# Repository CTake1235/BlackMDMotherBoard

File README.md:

# 黒MDマザーボード設計構想
> by しーたけ @C_Take_e
> since 2024/03/05
## 黒MDとは？
```
茨城高専ロボット部にて2017年に開発・製造されたMD。レジストが黒いのでそう呼ばれている。
定格12V駆動。I2C信号またはRS-485で動作する（基本I2Cでしか使わん）。
ロボコンで用いる各種モータを振り回せるため、何も考えずに使いまわされ続けている。
```
## コンセプト
- **やさしいマザボ**
## 詳細な構想
- ケーブルを介した連結が可能な、4枚挿しコンパクトマザボ
	- 単純なケーブルでできる、「マザー連結用」のようなケーブルを不要とする
	
- 黒MD初期マザーに準拠したコネクタ配線
- XAコネクタとXT60コネクタ（現在部活で主流のもの）を用いる
- 電源系の配線はタテ、信号系はヨコ
	- 電源系をヨコにすると、水平方向に広げる回路ボックスと相性が悪い
		- 縦に広がる回路ボックス: 基板を縦に積みつつコネクタを横に出して省面積化できる
		- 横に広がる回路ボックス(現在): 基板を水平方向に並べるので、コネクタがヨコ向きだとほかの基板と干渉するなど問題が起きやすい
	- 信号系はタテにすると基板の配置上MDとツメロック部分が干渉するなど、かえって邪魔になる
		- また、信号線は電源線に比べて細く曲げやすいため、ケーブルが他の基板などと干渉しにくい
- 100mm \* 100mmに収める
	- これは発注金額の問題
	- 実際には1.27(0.5mil)の倍数: 99.06mmを1辺とする設計にすることで配線の対称性などを保つ
- https://www.figma.com/file/h6nRyaCE1Uanp6SJ3a7Op9/2024%E9%BB%92MD%E3%83%9E%E3%82%B6%E3%83%BC?type=whiteboard&node-id=0%3A1&t=XtIcsm7LwBn8oLYL-1
	- figmaに謎図あります

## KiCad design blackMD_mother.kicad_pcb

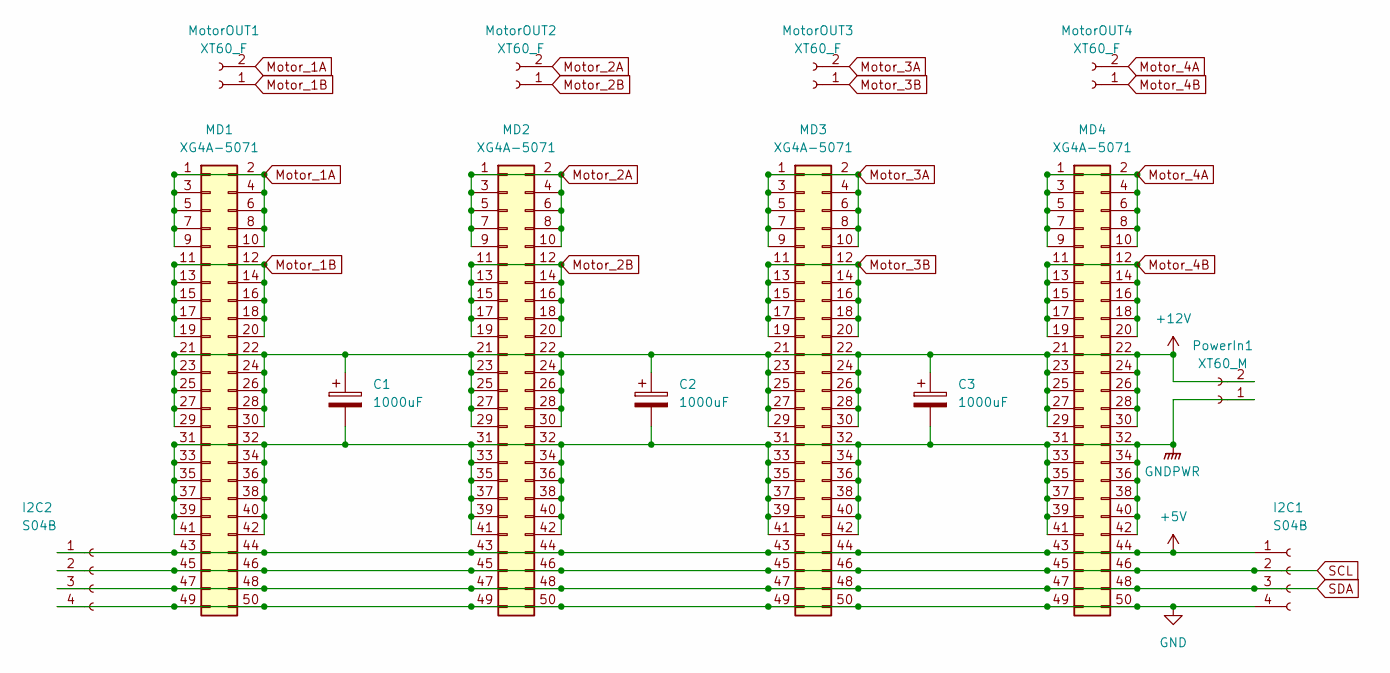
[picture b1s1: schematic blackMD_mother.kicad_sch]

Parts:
C1, C2, C3: 1000uF; CP_Radial_D10.0mm_P5.00mm
I2C1, I2C2: S04B; JST_XA_S04B-XASK-1_1x04_P2.50mm_Horizontal
MD1, MD2, MD3, MD4: XG4A-5071; PinSocket_2x25_P2.54mm_Vertical
MotorOUT1, MotorOUT2, MotorOUT3, MotorOUT4: XT60_F; AMASS_XT60-F_1x02_P7.20mm_Vertical
PowerIn1: XT60_M; AMASS_XT60-M_1x02_P7.20mm_Vertical

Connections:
+5V: I2C1.1, I2C2.1, MD1.43, MD1.44, MD2.43, MD2.44, MD3.43, MD3.44, MD4.43, MD4.44
+12V: C1.1, C2.1, C3.1, MD1.21, MD1.22, MD1.23, MD1.24, MD1.25, MD1.26, MD1.27, MD1.28, MD1.29, MD1.30, MD2.21, MD2.22, MD2.23, MD2.24, MD2.25, MD2.26, MD2.27, MD2.28, MD2.29, MD2.30, MD3.21, MD3.22, MD3.23, MD3.24, MD3.25, MD3.26, MD3.27, MD3.28, MD3.29, MD3.30, MD4.21, MD4.22, MD4.23, MD4.24, MD4.25, MD4.26, MD4.27, MD4.28, MD4.29, MD4.30, PowerIn1.2
GND: I2C1.4, I2C2.4, MD1.49, MD1.50, MD2.49, MD2.50, MD3.49, MD3.50, MD4.49, MD4.50
GNDPWR: C1.2, C2.2, C3.2, MD1.31, MD1.32, MD1.33, MD1.34, MD1.35, MD1.36, MD1.37, MD1.38, MD1.39, MD1.40, MD1.41, MD1.42, MD2.31, MD2.32, MD2.33, MD2.34, MD2.35, MD2.36, MD2.37, MD2.38, MD2.39, MD2.40, MD2.41, MD2.42, MD3.31, MD3.32, MD3.33, MD3.34, MD3.35, MD3.36, MD3.37, MD3.38, MD3.39, MD3.40, MD3.41, MD3.42, MD4.31, MD4.32, MD4.33, MD4.34, MD4.35, MD4.36, MD4.37, MD4.38, MD4.39, MD4.40, MD4.41, MD4.42, PowerIn1.1
Motor_1A: MD1.1, MD1.2, MD1.3, MD1.4, MD1.5, MD1.6, MD1.7, MD1.8, MD1.9, MD1.10, MotorOUT1.2
Motor_1B: MD1.11, MD1.12, MD1.13, MD1.14, MD1.15, MD1.16, MD1.17, MD1.18, MD1.19, MD1.20, MotorOUT1.1
Motor_2A: MD2.1, MD2.2, MD2.3, MD2.4, MD2.5, MD2.6, MD2.7, MD2.8, MD2.9, MD2.10, MotorOUT2.2
Motor_2B: MD2.11, MD2.12, MD2.13, MD2.14, MD2.15, MD2.16, MD2.17, MD2.18, MD2.19, MD2.20, MotorOUT2.1
Motor_3A: MD3.1, MD3.2, MD3.3, MD3.4, MD3.5, MD3.6, MD3.7, MD3.8, MD3.9, MD3.10, MotorOUT3.2
Motor_3B: MD3.11, MD3.12, MD3.13, MD3.14, MD3.15, MD3.16, MD3.17, MD3.18, MD3.19, MD3.20, MotorOUT3.1
Motor_4A: MD4.1, MD4.2, MD4.3, MD4.4, MD4.5, MD4.6, MD4.7, MD4.8, MD4.9, MD4.10, MotorOUT4.2
Motor_4B: MD4.11, MD4.12, MD4.13, MD4.14, MD4.15, MD4.16, MD4.17, MD4.18, MD4.19, MD4.20, MotorOUT4.1
SCL: I2C1.2, I2C2.2, MD1.45, MD1.46, MD2.45, MD2.46, MD3.45, MD3.46, MD4.45, MD4.46
SDA: I2C1.3, I2C2.3, MD1.47, MD1.48, MD2.47, MD2.48, MD3.47, MD3.48, MD4.47, MD4.48

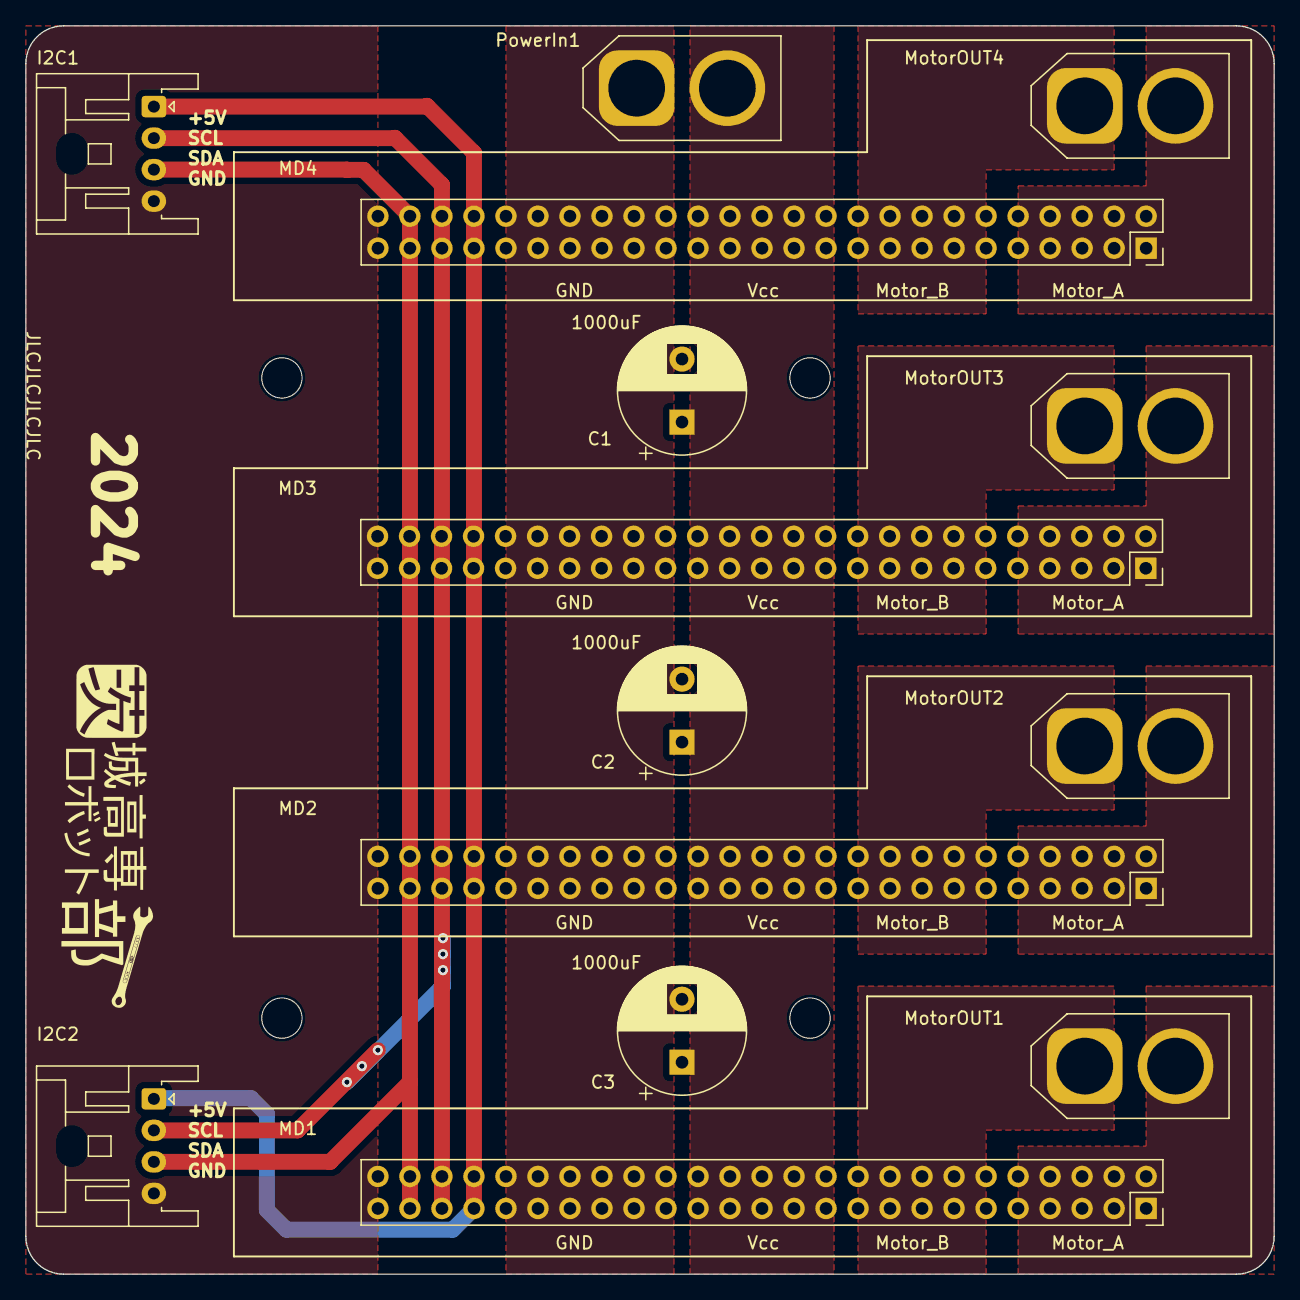
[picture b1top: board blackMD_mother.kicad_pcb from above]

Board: 2 copper layers, 99.1 x 99.1 mm, 14 parts (0 on the bottom side), 14 nets.

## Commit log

2024-03-06 update: mono.pdf
2024-03-06 update: PDFs, GBRs
2024-03-06 change: fillet corners
2024-03-06 update: PDFs & GBRs
2024-03-06 change: XAconnector, horizontal to vertical; This commit includes PDFs & GBRs changes
2024-03-06 change README
2024-03-06 add: README, link to figma
2024-03-06 change: width of GNDPWR
2024-03-07 Revert "change: width of GNDPWR"
    This reverts commit 1e5340b1a1ce9a68678be1db281a547735c12933.
2024-03-07 swap MotorA & MotorB
2024-03-07 update PDFs & GBRs
2024-03-07 add JLC
2024-03-07 update silk
2024-03-07 keep more clearance between +5V & GNDPWR
2024-03-07 add note about MD
